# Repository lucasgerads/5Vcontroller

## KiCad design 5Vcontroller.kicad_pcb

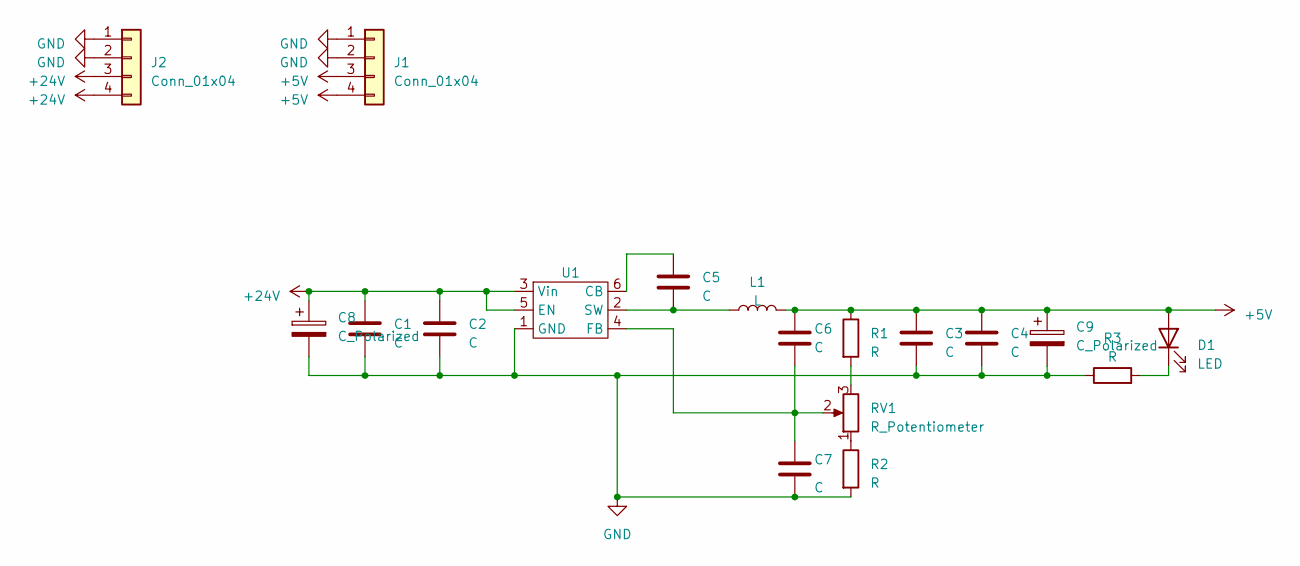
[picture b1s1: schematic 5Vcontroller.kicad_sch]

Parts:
C1, C2: C; C_1812_4532Metric
C3, C4, C5: C; C_1206_3216Metric
C6, C7: C; C_0805_2012Metric
C8, C9: C_Polarized; CP_Elec_8x5.4
D1: LED; LED_1206_3216Metric
J1, J2: Conn_01x04; PinHeader_1x04_P2.54mm_Vertical
L1: L; 13R682C
R1, R2, R3: R; R_1206_3216Metric
RV1: R_Potentiometer; Potentiometer_Vishay_T7-YA_Single_Vertical
U1: SOT-23-6

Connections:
+5V: C3.1, C4.1, C6.1, C9.1, D1.2 (A), J1.3, J1.4, L1.2, R1.1
+24V: C1.1, C2.1, C8.1, J2.3, J2.4, U1.3 (Vin), U1.5 (EN)
GND: C1.2, C2.2, C3.2, C4.2, C7.2, C8.2, C9.2, J1.1, J1.2, J2.1, J2.2, R2.2, R3.1, U1.1 (GND)
unnamed: D1.1 (K), R3.2
unnamed: R1.2, RV1.3
unnamed: R2.1, RV1.1
unnamed: C5.1, U1.6 (CB)
unnamed: C6.2, C7.1, RV1.2, U1.4 (FB)
unnamed: C5.2, L1.1, U1.2 (SW)

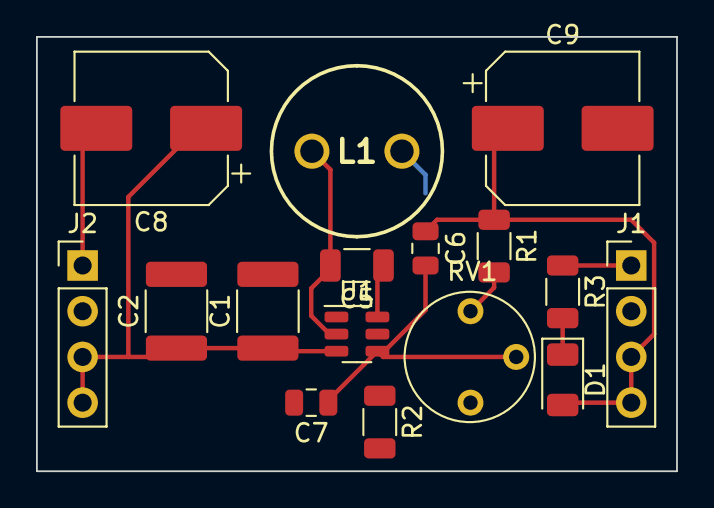
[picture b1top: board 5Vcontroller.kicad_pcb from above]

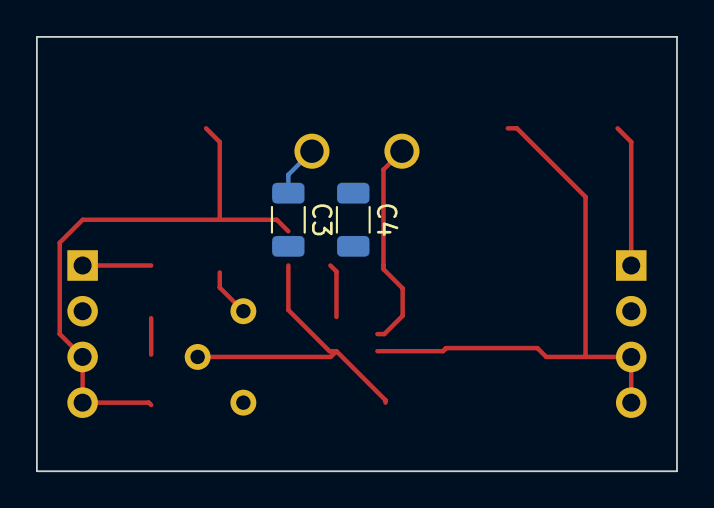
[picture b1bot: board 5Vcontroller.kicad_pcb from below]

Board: 2 copper layers, 35.6 x 24.1 mm, 18 parts (2 on the bottom side), 9 nets.
